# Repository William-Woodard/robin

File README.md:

# Robin PCB

Over Christmas 2022 I made 20 Christmas themed Robin PCBs. Powered by an Attiny85, each PCB has 5 neopixels so show pretty patterns and a buzzer so it can play Christmas music. They have 2 AA batteries and an off switch meaning they should last longer than last years!

## Robin Instructions

Turn the Robin on or off with the button located on the tail. Every time you turn it on it rotates between 2 different patterns. To make it play music, press firmly on one of the spots marked below. You may have to have slightly sweaty hands for it to work :)

Instead of having 3 buttons for the Christmas songs, I connected 3 of the gpios from the microcontroller to 3 exposed copper pads on the pcb (the eye and the 2 beaks). These are pulled high by a 200k resistor but if you press between the copper pad and ground as shown in the diagram below, you pull the voltage down as current flows through the moisture on your finger. The microcontroller detects that the voltage is reduced so plays a song.

## The assembly process

* I first used a stencil to apply solder paste to the robin
* I then used tweesers to place all the parts onto the board
* I used a hot plate to reflow solder all the components

* I used a soldering iron to attach both the battery holder (through hole) and the buzzer (on the opposite side to the rest of the components)
* I used an arduino to program the microcontroller via spi

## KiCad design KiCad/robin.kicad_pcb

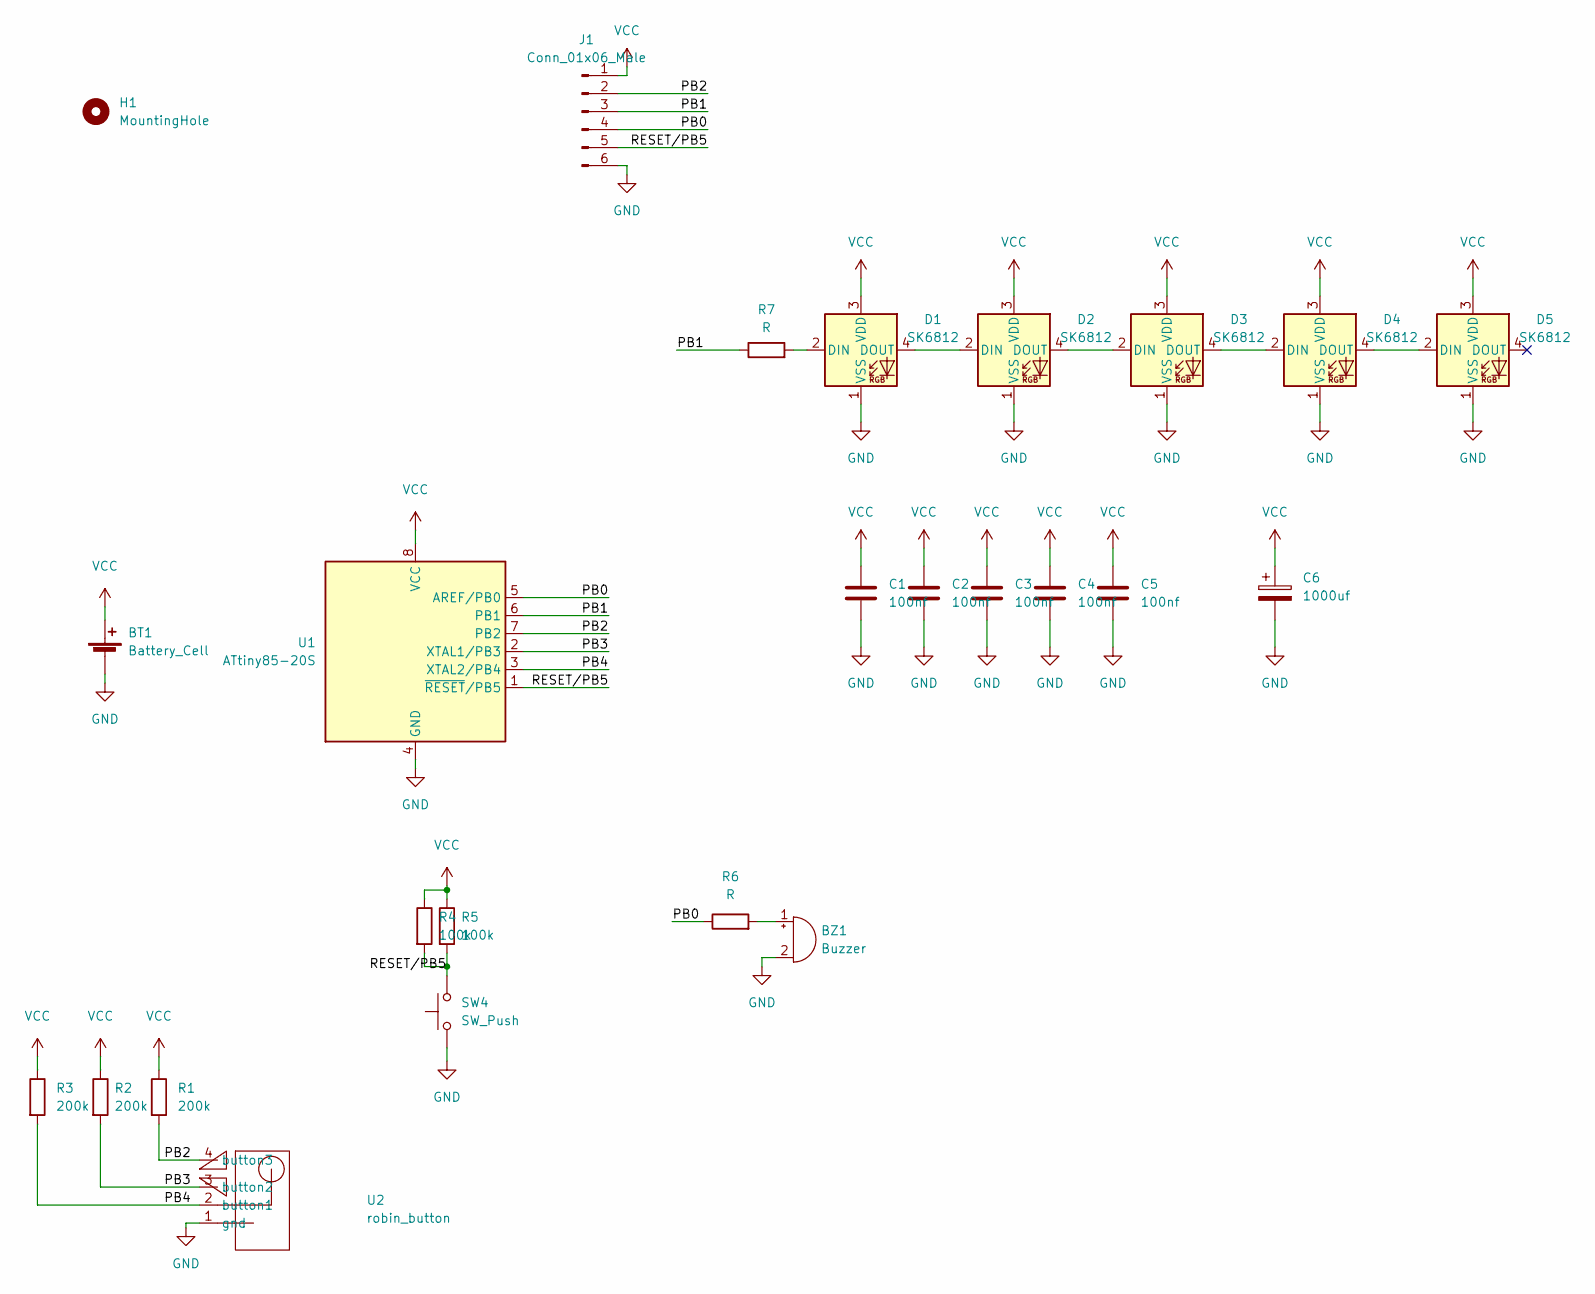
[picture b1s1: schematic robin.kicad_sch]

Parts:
BT1: Battery_Cell; BatteryHolder_Keystone_2462_2xAA
BZ1: Buzzer; Buzzer_CUI_CPT-9019S-SMT
C1, C2, C3, C4, C5: 100nf; C_0805_2012Metric_Pad1.18x1.45mm_HandSolder
C6: 1000uf; CP_Radial_D8.0mm_P5.00mm
D1, D2, D3, D4, D5: SK6812; LED_SK6812_PLCC4_5.0x5.0mm_P3.2mm
H1: MountingHole; MountingHole_3mm_Pad_Via
J1: Conn_01x06_Male; PinSocket_2x03_P2.54mm_Vertical
R1, R2, R3: 200k; R_0603_1608Metric
R4, R5: 100k; R_0603_1608Metric
R6, R7: R; R_0603_1608Metric
SW4: SW_Push; SW_SPST_B3S-1000
U1: ATtiny85-20S; SOIC-8W_5.3x5.3mm_P1.27mm
U2: robin_button; copp27

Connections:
/PB0: J1.4, R6.1, U1.5 (AREF/PB0)
/PB1: J1.3, R7.1, U1.6 (PB1)
/PB2: J1.2, R1.2, U1.7 (PB2), U2.4 (button3); also elsewhere on the board
/PB3: R2.2, U1.2 (XTAL1/PB3), U2.3 (button2); also elsewhere on the board
/PB4: R3.2, U1.3 (XTAL2/PB4), U2.2 (button1); also elsewhere on the board
/RESET/PB5: J1.5, R4.2, R5.2, SW4.2, U1.1 (~RESET/PB5)
GND: BT1.2 (-), BZ1.2 (+), C1.2, C2.2, C3.2, C4.2, C5.2, C6.2, D1.1 (VSS), D2.1 (VSS), D3.1 (VSS), D4.1 (VSS), D5.1 (VSS), J1.6, SW4.1, U1.4 (GND), U2.1 (gnd); also elsewhere on the board
unnamed: BZ1.1 (-), R6.2
unnamed: D1.2 (DIN), R7.2
unnamed: D1.4 (DOUT), D2.2 (DIN)
unnamed: D2.4 (DOUT), D3.2 (DIN)
unnamed: D3.4 (DOUT), D4.2 (DIN)
unnamed: D4.4 (DOUT), D5.2 (DIN)
VCC: BT1.1 (+), C1.1, C2.1, C3.1, C4.1, C5.1, C6.1, D1.3 (VDD), D2.3 (VDD), D3.3 (VDD), D4.3 (VDD), D5.3 (VDD), J1.1, R1.1, R2.1, R3.1, R4.1, R5.1, U1.8 (VCC)

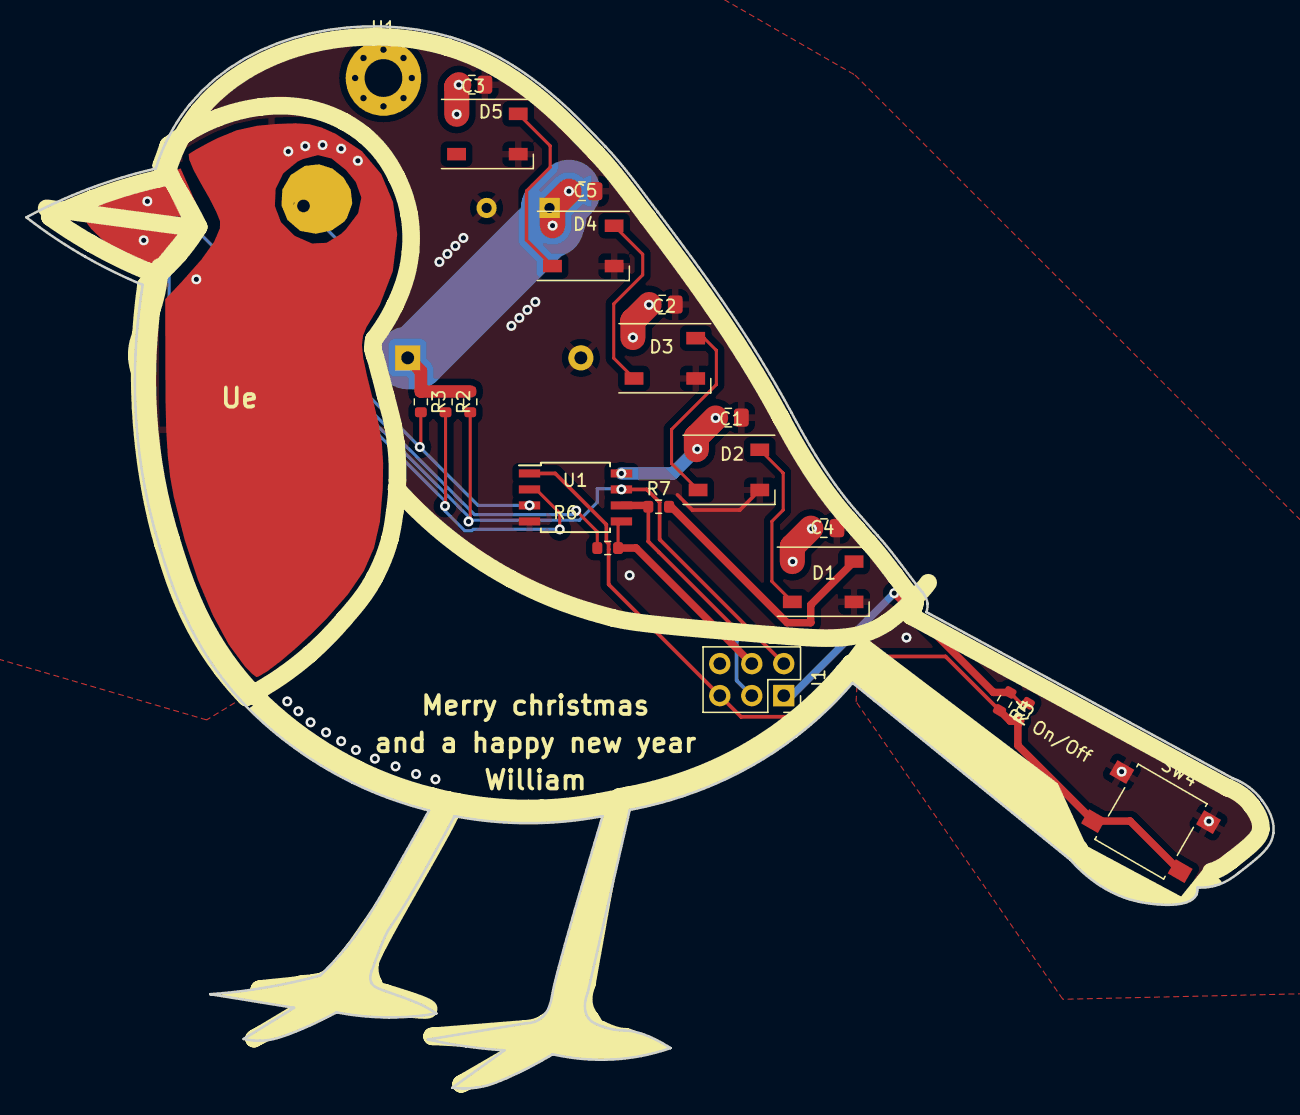
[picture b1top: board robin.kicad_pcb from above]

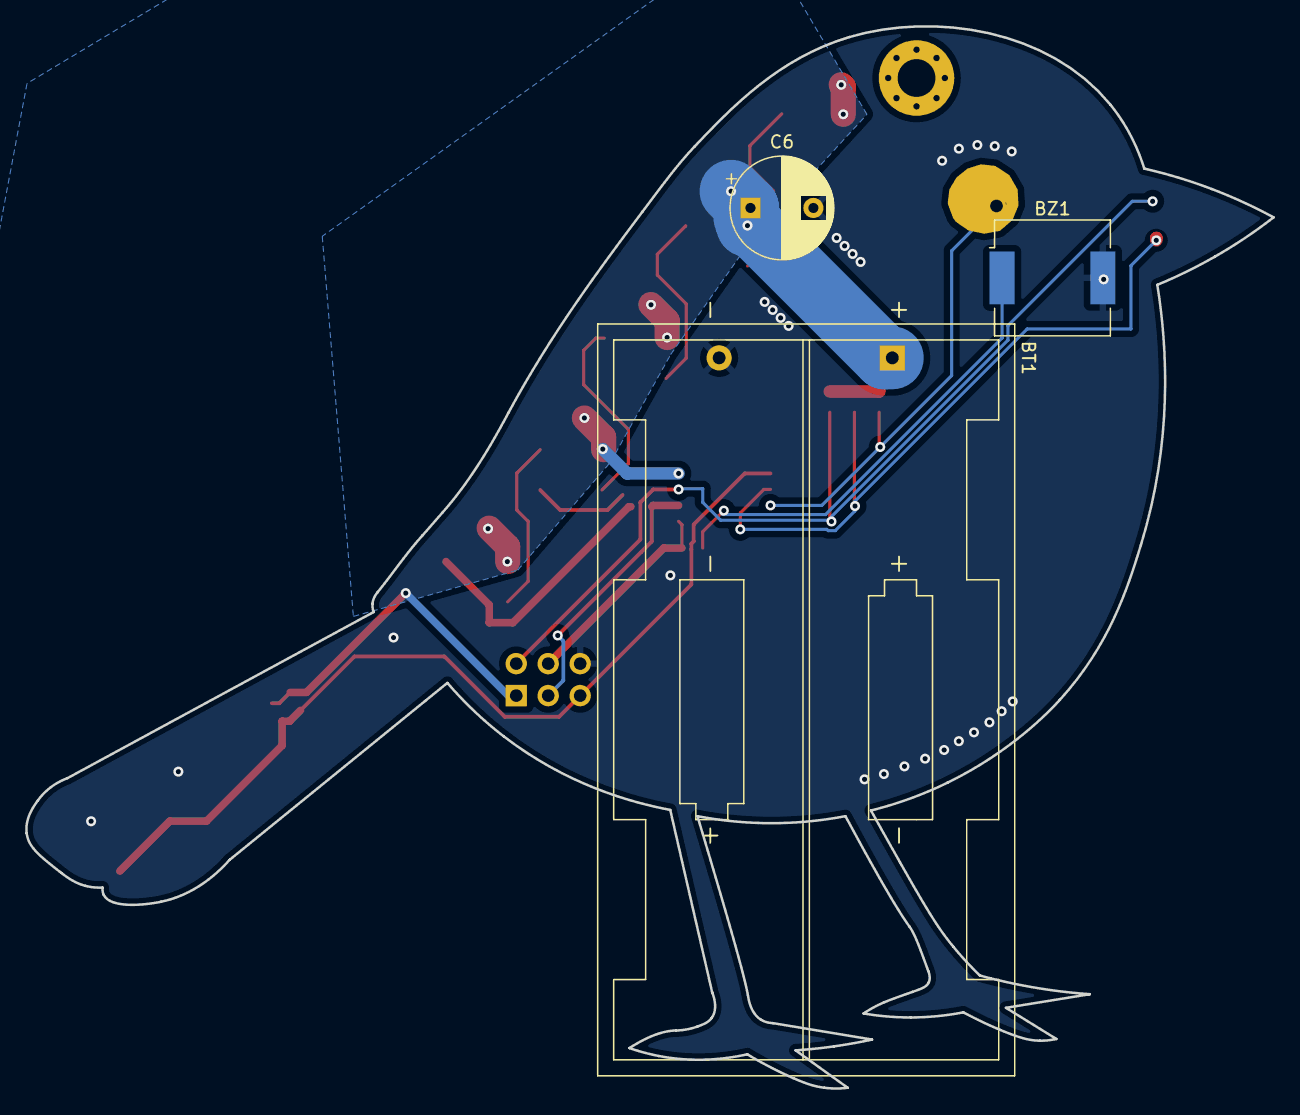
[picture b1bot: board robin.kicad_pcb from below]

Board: 2 copper layers, 99.1 x 84.4 mm, 25 parts (3 on the bottom side), 14 nets.

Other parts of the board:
Ue: robin_button; copp27

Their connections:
/PB2: Ue.4 (button3); also elsewhere on the board
/PB3: Ue.3 (button2); also elsewhere on the board
/PB4: Ue.2 (button1); also elsewhere on the board
GND: Ue.1 (gnd); also elsewhere on the board

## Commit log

2023-01-04 Added untidy code
2023-01-04 Removed images from arduino example
2023-01-04 Added KiCad files
2023-01-06 added instructions
2023-01-06 added picture of robin on the hot plate
2023-01-06 Tidied the code (slightly)
